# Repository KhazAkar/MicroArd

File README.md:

# MicroArd
It's development board/breakout board with FT230XQ USB-UART interface IC adapted for UPDI interface used to program newest series of Microchip AVR utility.
This board is compatible with pyudpi software, used for programming that MCU.

## License

Original hardware designs: **CERN-OHL-S-2.0**. See [LICENSE](LICENSE)
for the full terms and [NOTICE](NOTICE) for attribution and scope.
Third-party library content, CAD and datasheets retain their own terms.

Source location: https://gitlab.com/r3xxar/MicroArd

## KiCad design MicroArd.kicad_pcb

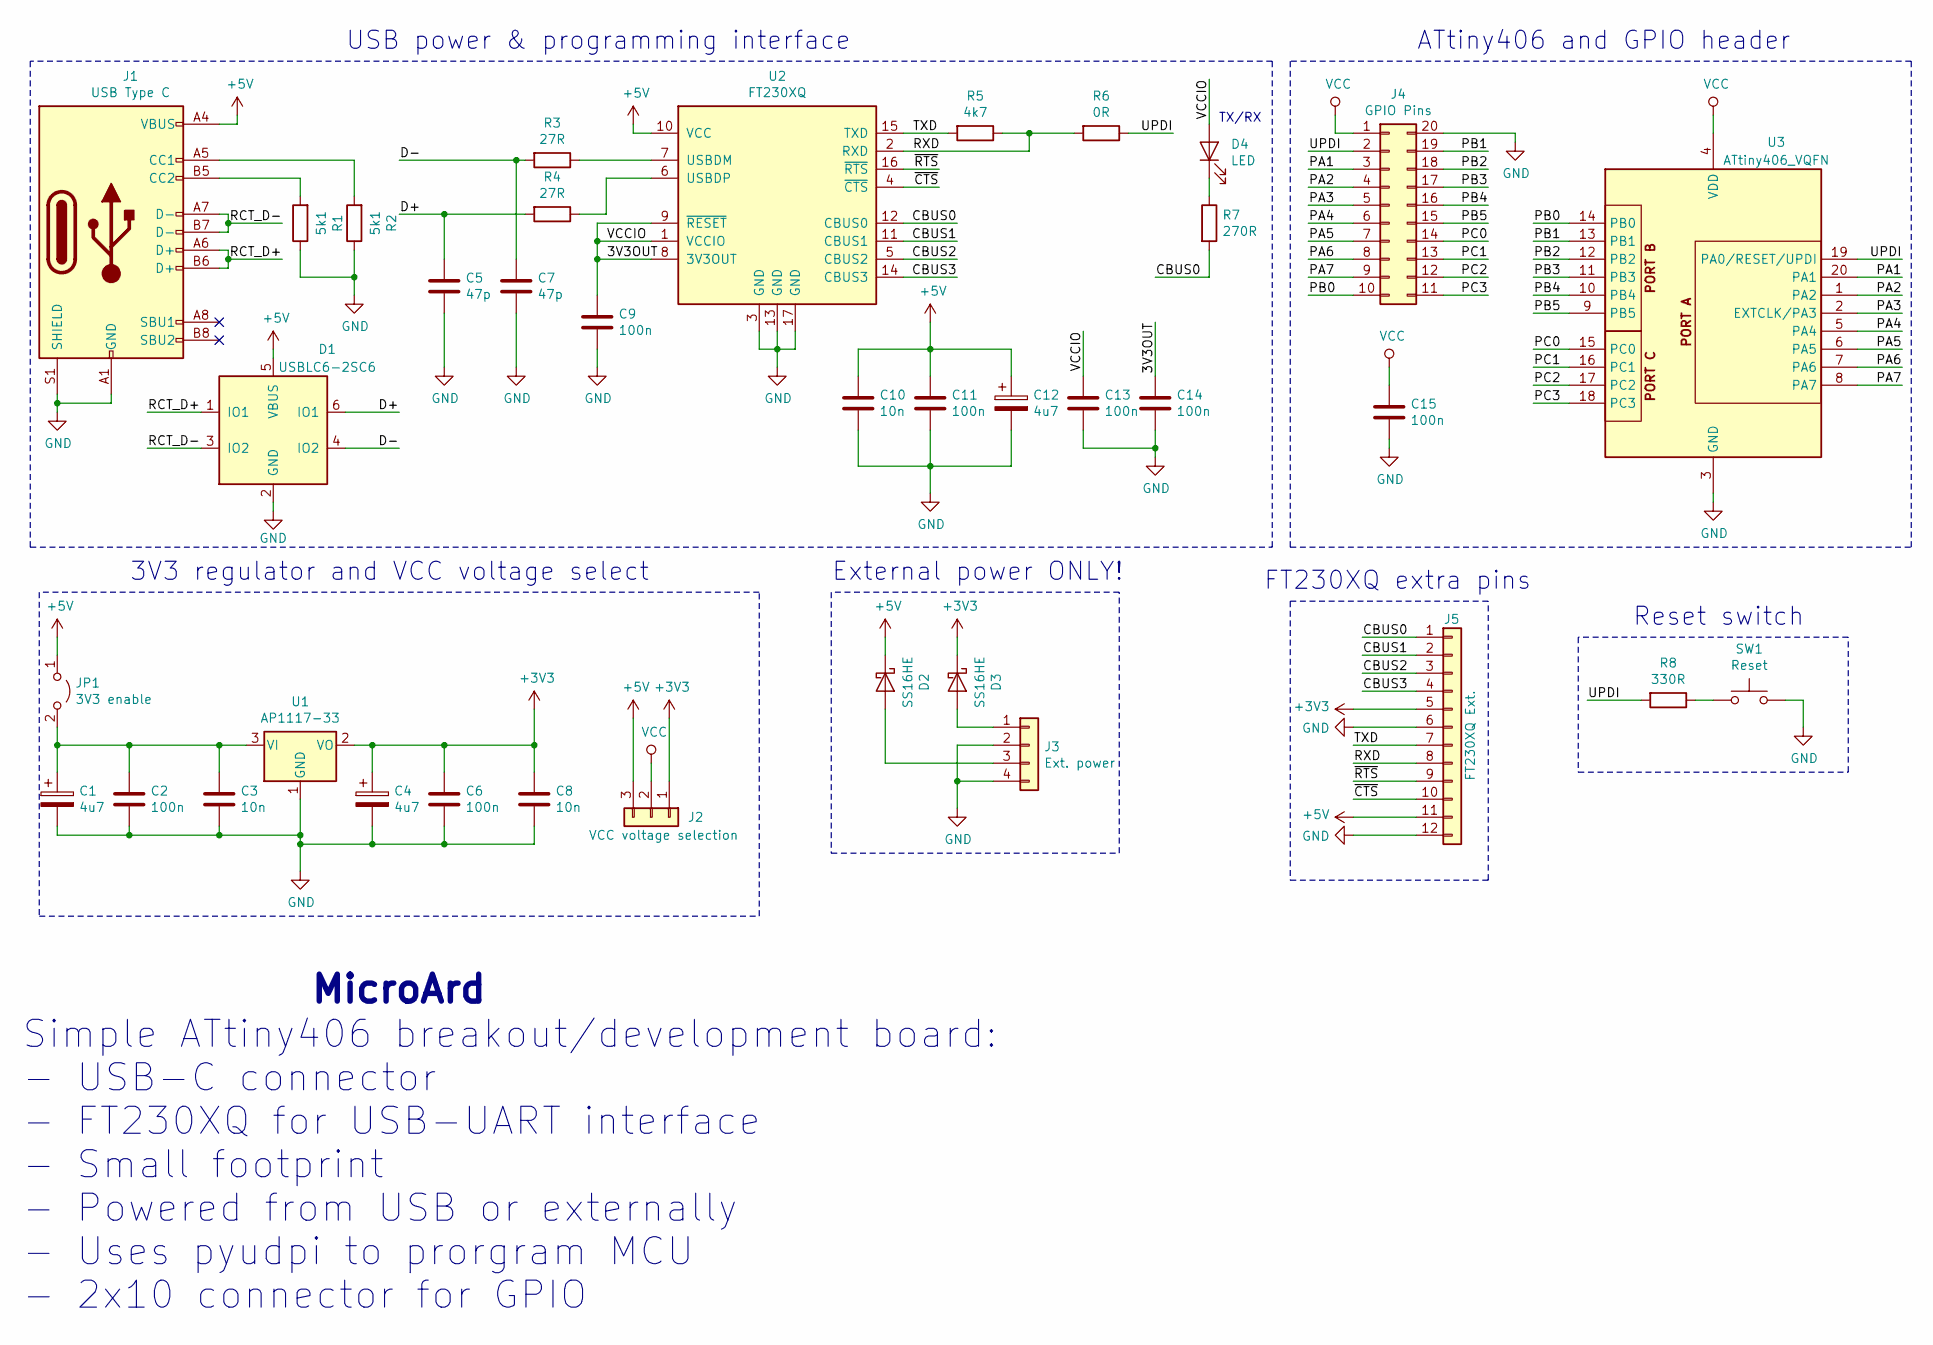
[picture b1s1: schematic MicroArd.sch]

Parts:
C1, C4, C12: 4u7; CP_EIA-3216-18_Kemet-A_Pad1.58x1.35mm_HandSolder
C2, C6, C9, C11, C13, C14, C15: 100n; C_0603_1608Metric_Pad1.05x0.95mm_HandSolder
C3, C8, C10: 10n; C_0603_1608Metric_Pad1.05x0.95mm_HandSolder
C5, C7: 47p; C_0603_1608Metric_Pad1.05x0.95mm_HandSolder
D1: USBLC6-2SC6; SOT-23-6_Handsoldering
D2, D3: SS16HE; D_SOD-323_HandSoldering
D4: LED; LED_0805_2012Metric_Pad1.15x1.40mm_HandSolder
J1: USB Type C; TE_2129691-1
J2: VCC voltage selection; PinHeader_1x03_P2.54mm_Vertical
J3: Ext. power; PinHeader_1x04_P2.54mm_Vertical
J4: GPIO Pins; PinHeader_2x10_P2.54mm_Vertical
J5: FT230XQ Ext.; PinHeader_1x12_P2.54mm_Vertical
JP1: 3V3 enable; PinHeader_1x02_P2.54mm_Vertical
R1, R2: 5k1; R_0603_1608Metric_Pad1.05x0.95mm_HandSolder
R3, R4: 27R; R_0603_1608Metric_Pad1.05x0.95mm_HandSolder
R5: 4k7; R_0603_1608Metric_Pad1.05x0.95mm_HandSolder
R6: 0R; R_0603_1608Metric_Pad1.05x0.95mm_HandSolder
R7: 270R; R_0603_1608Metric_Pad1.05x0.95mm_HandSolder
R8: 330R; R_0603_1608Metric_Pad1.05x0.95mm_HandSolder
SW1: Reset; SW_PUSH_6mm_H4.3mm
U1: AP1117-33; SOT-223-3_TabPin2
U2: FT230XQ; QFN-16-1EP_4x4mm_P0.65mm_EP2.1x2.1mm
U3: ATtiny406_VQFN; QFN-20-1EP_3x3mm_P0.4mm_EP1.65x1.65mm

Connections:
+3V3: C4.1, C6.1, C8.1, D3.1 (K), J2.1, J5.5, U1.2 (VO)
+5V: C10.1, C11.1, C12.1, D1.5 (VBUS), D2.1 (K), J1.A4 (VBUS), J1.A9 (VBUS), J1.B4 (VBUS), J1.B9 (VBUS), J2.3, J5.11, JP1.1 (A), U2.10 (VCC)
/3V3OUT: C9.1, C13.1, C14.1, D4.2 (A), U2.1 (VCCIO), U2.8 (3V3OUT), U2.9 (~RESET)
/CBUS0: J5.1, R7.2, U2.12 (CBUS0)
/CBUS1: J5.2, U2.11 (CBUS1)
/CBUS2: J5.3, U2.5 (CBUS2)
/CBUS3: J5.4, U2.14 (CBUS3)
/D+: C5.1, D1.6 (IO1), R4.2
/D-: C7.1, D1.4 (IO2), R3.2
/PA1: J4.3, U3.20 (PA1)
/PA2: J4.4, U3.1 (PA2)
/PA3: J4.5, U3.2 (EXTCLK/PA3)
/PA4: J4.6, U3.5 (PA4)
/PA5: J4.7, U3.6 (PA5)
/PA6: J4.8, U3.7 (PA6)
/PA7: J4.9, U3.8 (PA7)
/PB0: J4.10, U3.14 (PB0)
/PB1: J4.19, U3.13 (PB1)
/PB2: J4.18, U3.12 (PB2)
/PB3: J4.17, U3.11 (PB3)
/PB4: J4.16, U3.10 (PB4)
/PB5: J4.15, U3.9 (PB5)
/PC0: J4.14, U3.15 (PC0)
/PC1: J4.13, U3.16 (PC1)
/PC2: J4.12, U3.17 (PC2)
/PC3: J4.11, U3.18 (PC3)
/RCT_D+: D1.1 (IO1), J1.A6 (D+), J1.B6 (D+)
/RCT_D-: D1.3 (IO2), J1.A7 (D-), J1.B7 (D-)
/RXD: J5.8, R5.1, R6.2, U2.2 (RXD)
/TXD: J5.7, R5.2, U2.15 (TXD)
/UPDI: J4.2, R6.1, R8.2, U3.19 (PA0/RESET/UPDI)
/~CTS: J5.10, U2.4 (~CTS)
/~RTS: J5.9, U2.16 (~RTS)
GND: C1.2, C2.2, C3.2, C4.2, C5.2, C6.2, C7.2, C8.2, C9.2, C10.2, C11.2, C12.2, C13.2, C14.2, C15.2, D1.2 (GND), J1.A1 (GND), J1.A12 (GND), J1.B1 (GND), J1.B12 (GND), J1.S1 (SHIELD), J3.2, J3.4, J4.20, J5.6, J5.12, R1.1, R2.1, SW1.2, U1.1 (GND), U2.3 (GND), U2.13 (GND), U2.17 (GND), U3.3 (GND)
unnamed: C1.1, C2.1, C3.1, JP1.2 (B), U1.3 (VI)
unnamed: D2.2 (A), J3.3
unnamed: D3.2 (A), J3.1
unnamed: D4.1 (K), R7.1
unnamed: J1.A5 (CC1), R2.2
unnamed: J1.B5 (CC2), R1.2
unnamed: R3.1, U2.7 (USBDM)
unnamed: R4.1, U2.6 (USBDP)
unnamed: R8.1, SW1.1
VCC: C15.1, J2.2, J4.1, U3.4 (VDD)

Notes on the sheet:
Simple ATtiny406 breakout/development board: - USB-C connector - FT230XQ for USB-UART interface - Small footprint - Powered from USB or externally - Uses pyudpi to prorgram MCU - 2x10 connector for GPIO
ATtiny406 and GPIO header
External power ONLY!
USB power & programming interface
3V3 regulator and VCC voltage select
MicroArd
TX/RX
FT230XQ extra pins
Reset switch

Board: 4 copper layers, 37 parts (0 on the bottom side), 44 nets, no tracks yet.

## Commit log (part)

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2019-09-11 Add README
2019-09-16 Schematic is complete, now PCB! Around 40mm x 50 mm in dimensions
2019-09-19 Fix silly bug with USB lines, add reset button and start PCB part placement :)
2019-10-08 Little update to PCB
2019-11-08 Change from 2 layer to 4 layer, minior updates to PCB and schematic
